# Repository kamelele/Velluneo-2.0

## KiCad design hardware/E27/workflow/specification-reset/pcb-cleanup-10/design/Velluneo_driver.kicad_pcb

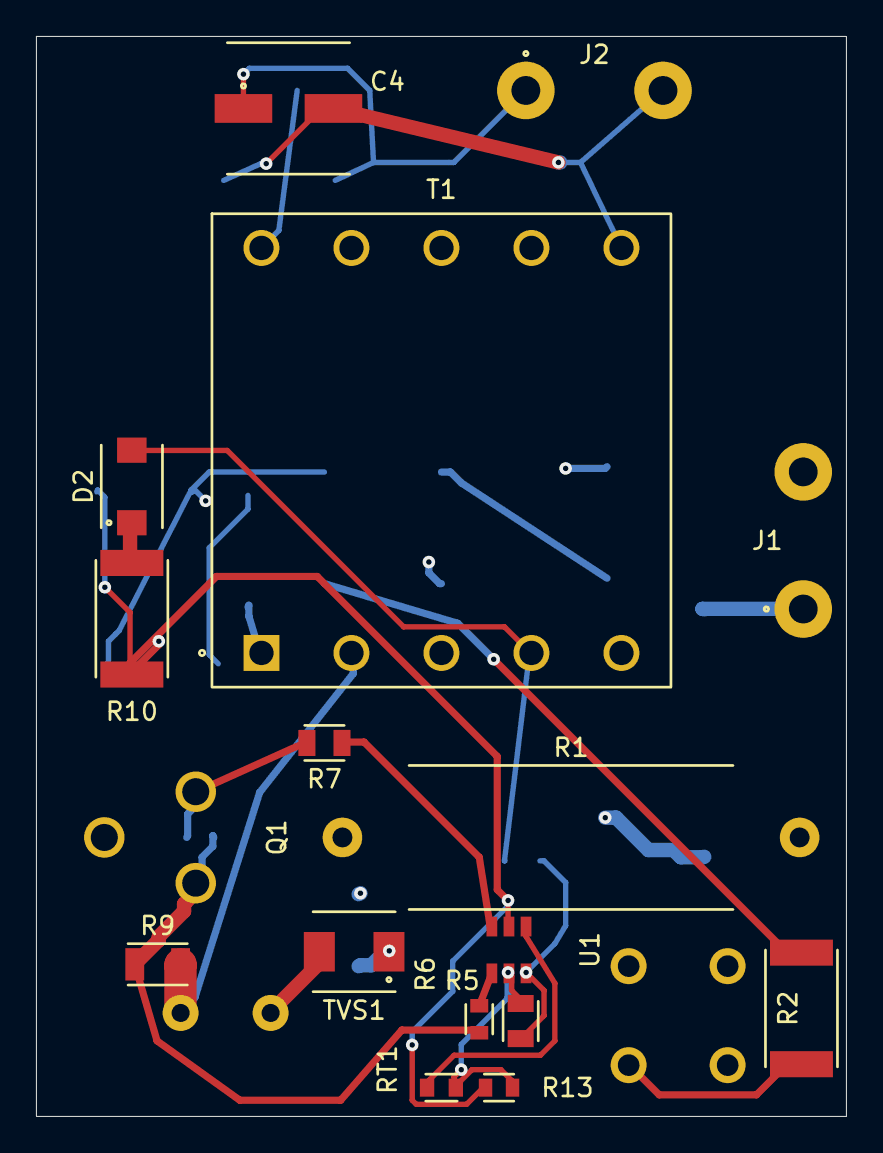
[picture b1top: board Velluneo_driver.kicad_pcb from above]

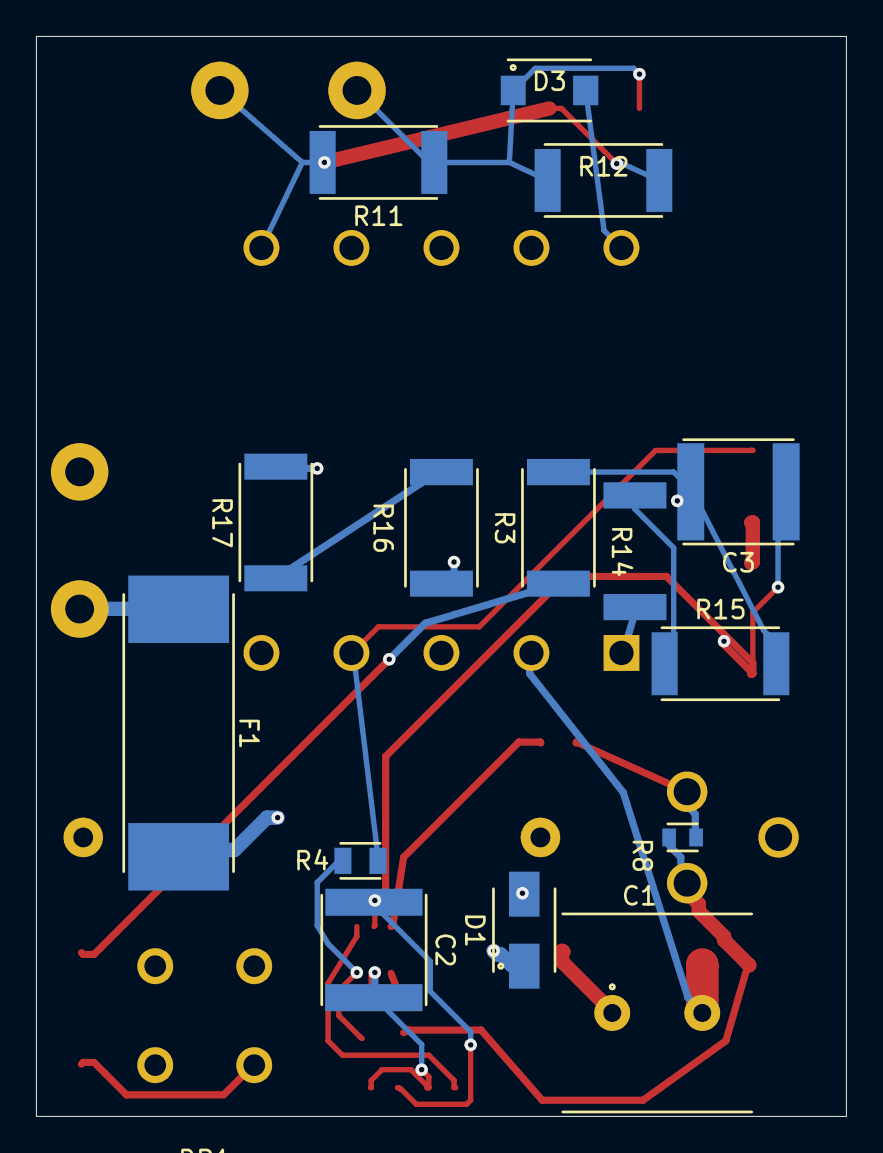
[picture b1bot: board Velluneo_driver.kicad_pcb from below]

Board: 4 copper layers, 45.0 x 60.0 mm, 33 parts (16 on the bottom side), 23 nets.

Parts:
BR1: W10G-E4/51; W10G_Formed5p5_PROJECT
C1: 15u / 450V; Rubycon_BXW_D10_P5_PROJECT_CANDIDATE
C2, C3: 470n / 50V C0G; KEMET_2220_C0G_DensityB_Native
C4: 10u / 63V HYBRID; Panasonic_ZA_D_Standard_Native
D1: US1M-13-F; Diodes_US1M_SMA_Native
D2: STTH1R02A; ST_STTH_SMA_Native
D3: STTH2R02A; ST_STTH_SMA_Native
F1: 250mA / 277VAC; SCHURTER_UMTH_WEB_PROVISIONAL
J1: E27 INTERNAL WIRES; InternalWirePair_P7p62_D1p6_PROJECT_CANDIDATE
J2: INTERNAL LED WIRES; InternalWirePair_P7p62_D1p6_PROJECT_CANDIDATE
Q1: STF2N80K5; STF2N80K5_Stagger5p08_Pad2p25_PROJECT
R1: 47R / AC05; AC05_P25p4_FORMED_PROJECT_CANDIDATE
R2, R3, R15: 499k; CRCW_2512_NativeReflow
R4: 80.6k; CRCW_0805_NativeReflow
R5: 17.4k; CRCW_0805_NativeReflow
R6: 1.40k; CRCW_0603_NativeReflow
R7: 4.7R; CRCW_0805_NativeReflow
R8: 47k; CRCW_0603_NativeReflow
R9: 2.32R / PROPOSED; CRCW_1206_NativeReflow
R10: 4.7R; CRCW_2512_NativeReflow
R11, R12: 20k; CRCW_2512_NativeReflow
R13: 80.6k / feed bleeder; CRCW_0603_NativeReflow
R14: 499k; CRCW_2512_R14_SilkClear
R16, R17: 402k / startup; CRCW_2512_NativeReflow
RT1: 100k / B4100; NTCS0603_NativeReflow
T1: 120:30:22 / 2.304mH; TDK_EFD25_Pad2p0_PROJECT
TVS1: SMBJ160A-E3/52; Vishay_SMBJ_PROJECT_CANDIDATE
U1: UCC28701DBVR; UCC28701_DBV_Native

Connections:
/AUX_RAW: D2.2, R4.1, T1.4
/BLEED_MID_B: R14.2, R15.1
/BULK_POS: BR1.1, C1.1, R2.1, R14.1, R16.1, T1.1, TVS1.2
/CS: R6.2, U1.4
/DRAIN: D1.2, Q1.2, T1.5
/DRV: R7.1, U1.3
/GATE: Q1.1, R7.2, R8.1
/NTC: RT1.1, U1.1
/OUTPUT_NEG: C4.2, J2.2, R11.2, R12.2, T1.6
/OUTPUT_POS: C4.1, D3.1, J2.1, R11.1, R12.1
/PRIMARY_GND: BR1.3, C1.2, C2.2, C3.2, R3.2, R5.2, R9.2, R13.2, R15.2, RT1.2, T1.2, U1.5
/SECONDARY_RAW: D3.2, T1.10
/SENSE: Q1.3, R6.1, R8.2, R9.1
/STARTUP_MID: R16.2, R17.1
/VDD: C2.1, C3.1, R10.2, R13.1, R17.2, U1.2
/VS: R4.2, R5.1, U1.6
unnamed: BR1.2, J1.2
unnamed: BR1.4, R1.2
unnamed: D1.1, TVS1.1
unnamed: D2.1, R10.1
unnamed: F1.1, J1.1
unnamed: F1.2, R1.1
unnamed: R2.2, R3.1

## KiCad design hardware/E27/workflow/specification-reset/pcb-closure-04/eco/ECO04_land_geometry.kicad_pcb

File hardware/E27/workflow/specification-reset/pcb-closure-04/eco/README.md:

# ECO04 — concrete, unapplied spacing redesign

This is a **proposed33-part/81-pin electrical and terminal-construction change**, not the approved31-part driver and a complete proposed placed PCB, with no tracks. The separate native schematic, BOM, pre-CAD pin map, fresh81-pin/23-functional-net comparison and four footprint coupons are supplied for affected review. Human approval is absent. The improved31-part return-layout project in the parent directory still reports the eight package clearance findings.

## Exact proposed changes

- U1: UCC28711DR → **UCC28701DBVR**, a real no-HV-pin controller. New pin numbers are1NTC,2VDD,3DRV,4CS,5GND,6VS. Add R16/R17, each proposed402kΩ/2512, in series BULK_POS → STARTUP_MID → VDD. This physically removes the old high-voltage pin pair; it is not an artificial net rename or NC flag.
- R13: **80.6kΩ CRCW060380K6FKEA**, replacing1MΩ, forms a passive divider with804kΩ startup resistance. At normal253Vac and±2.1% resistor allowances, its zero-controller-current ceiling is33.8667V. This addresses the continuous startup-feed bound without assuming a minimum IC sink current. It is not a clamp on auxiliary/transient/surge injection.
- R9: proposed **2.32Ω E96 CRCW12062R32FKEA**, subject to procurement confirmation, replacing2.37Ω to account for the new CC constant. Nominal current changes about−1.25%, rather than falsely claiming pin-for-pin electrical equivalence. The earlier2.29Ω mathematical target was not silently treated as an available catalog part.
- BR1: **W10G-E4/51**, with a proposed formed5.5±0.05mm grid,2.0mm pads/1.2mm holes. Raw leads are not fixed5.08mm; forming/registration, polarity datum and supplier process require qualification. Nominal adjacent copper gap3.5mm, annulus0.4mm.
- Q1: **STF2N80K5**, G1/D2/S3, replacing the SOT223 device and separate drain-tab terminal. Proposed outer-terminal rowy0/centre drainy5.08mm at2.54mmx pitch,2.2mm pads/1.5mm holes. Nominal G-D and D-S gap3.479613mm; annulus0.35mm. Bend radius, root clearance, seating, strain, jig and installed height are unresolved process inputs.
- T1: proposed project lands2.0mm rather than2.4mm, with the same1.35mm finished holes and5mm pitch. Nominal annulus0.325mm and copper gap3.0mm. This is an explicit land redesign, not a source-prescribed qualified transformer or a claim that solder/registration tolerances leave3mm finished insulation.

The four isolated native land coupons have **zero native DRC violations**, with four unconnected items/exit5. They are not a functional supply. No3mm limit was reduced; primary/secondary remains10mm and STARTUP_MID is explicitly included as primary/HV in the proposed coupon rule scope. This result establishes nominal land geometry only. It does not clear the eight findings on the unchanged31-part driver or by itself prove a complete33-part placement; see the separately checked full-board r3 result below.

## Source and operating differences

[TI UCC2870x](https://www.ti.com/lit/ds/symlink/ucc28700.pdf), SLUSB41A, pp3–6/12/21/24: no-HV NTC variant, UVLO19–23V/on and7.7–8.45V/off, startup1.5µA maximum at18V, CC constant310/319/329mV, new120/130/140kHz ceiling. NTC0.95V/105µA are typical only; the old bounded NTC resistance window and106kHz magnetic/thermal assessment cannot transfer. Recommended temperature starts−20C. [TI DBV land example](https://www.ti.com/lit/pdf/mpds026), p2: six1.1×0.6mm pads,x±1.3/y±0.95/0. These facts require a real controller ECO, not a drop-in claim.

[Vishay W10G](https://www.vishay.com/docs/88769/w005g.pdf), document88769, pp1–3:1000V/1.5A family, rawleadØ0.71–0.81mm/pitch4.6–5.6mm. Its current/thermal test conditions are not transferred to the new forming/land process. [ST STF2N80K5](https://www.st.com/resource/en/datasheet/stf2n80k5.pdf), DS14533rev1, pp1–3/9–10:800V,4.5Ωmax at10V/1A, Qg5nCtyp/Ciss105pFtyp, rectangular lead max1.00×0.70mm. Proposed hole accommodates that section; it does not qualify formed leads or switching/thermal performance.

Native source download of ST timed out twice; source facts above were inspected through official PDF text and independently checked by the source implementer, not a fabricated locally hashed PDF. Coupon coordinates beyond manufacturer land examples are explicitly project constructions. Exact existing-source hashes and native artifacts are frozen with the packet.

## Corrected startup and current calculations

calculate.py includes **both C2/C3 directly across VDD**, total0.94µF, old R13=1MΩ for rejected proposals and proposed80.6kΩ for the revised circuit, plus reverse D2 leakage. The auxiliary series resistor is R10=4.7Ω. The first13.6MΩ suggestion is explicitly rejected: its equilibrium18.65V at207Vac cannot reach23V even without diode leakage. Revised804kΩ/80.6kΩ is screened over resistor±2.1%, capacitor±5%, diode3/20µA and0/5V bulk-drop assumptions. These are loaded DC charging calculations, not demonstrated mains startup or a complete guaranteed controller model. [STTH1R02 leakage data](https://www.st.com/resource/en/datasheet/stth1r02.pdf), DS4743rev4p2, is conditional on rated reverse voltage and25/125C.

The nominal current equation is RCS=VCCR×NPS×η/(2×Iout), including the factor2. New2.32Ω gives approximately0.2475A atNPS4/η0.9. Normal energy/DCM screens and gate-energy scale are calculated explicitly; they are not a guaranteed fault ceiling, core-loss, SOA, repetitive clamp or temperature result. No minimum controller fault draw is specified, so no guaranteed retry interval is invented.

## Acceptance boundary

Power/magnetic/thermal review must close new frequency/control/corners, actual VDD behavior, NTC/sensor faults and repetitive/fault stresses. Mechanical/process review must validate lead forming, polarity, tolerances, finished solder/hole/annulus/insulation and installed envelope. The coupon does not establish fit inside40x60 or an outerØ60x120 lamp. The complete proposed replacement PCB has now been drafted in isolation; independent review and the human intent decision are required before adoption and accepted routing. Passing ERC or coupon DRC supplies neither that decision nor electrical/safety qualification.

## R2 review correction — VDD feed ceiling and inventory

Independent Reality finding R-C04-01 identified a real omission after the first charging calculation: the4.42MΩ/1MΩ continuous feed has a66.01V zero-controller-current equilibrium at ideal high line. Passing a23V startup screen did not bound VDD. That resistor pair is rejected for adoption. R2 uses two402kΩ startup resistors and80.6kΩ bleed. The passive feed-only normal-line ceiling is33.8667V with±2.1% resistor allowances; the feed net current at35V is negative even with zero controller current. All64 declared loaded charging cases reach23V, worst0.251660s. These are actual executable DC screens, not mains/winding/fault/transient measurements.

High-line resistor dissipation increases from0.02896W to0.15923W atVDD0, an additional0.13027W that remains an explicit thermal/lifetime condition. No active regulator, invented minimum current or stability claim is used. The gate-drive/auxiliary source and transient ceiling, retry, newNTCparameters/140kHzbehavior and finishedconstruction remain open. Change review also caught a reproducibility defect: the coupon builder now preserves both local library-table entries needed by the separate proposed schematic. Native31-part driver CAD is unchanged by this review correction.

## R3 — complete proposed PCB, not just coupons

Velluneo_specification_reset.kicad_pro now opens the complete proposed **33-part/81-pad rectangular41x60mm PCB and matched schematic**. Full native KiCad10.0.6 DRC with schematic parity has **zero violations, zero parity findings and54unconnected items**. It exits5 because it is unrouted, with zero tracks/vias. Coupon results remain separate. No global numeric clearance limit or source severity was weakened:3mm functional screen,10mm P/S reservation including allNC,0.25mm general and0.5mm copper-edge remain. Every loaded/reloaded pad shape/attribute/drill/layer/position, MPN/value/FPID/net and canonical pre-CAD intent agrees; source-module hashes bind the planning inventory. The original eight reports remain only on the retained old31-part comparison board, not on this new candidate.

The full proposal passes0.1mm same-face courtyard,0.4mm opposite THT-joint allowance, full30x30mm T1 allocation/semiconductor exclusion and all81-pad shape-aware common-copper checks. Independent native positive/negative circle controls confirm nominal Q1gap3.479613mm versus deliberate2.708319mm failure under the unchanged3mm rule. The deliberate negative fixture also reports the expected library mismatch; no production module was changed by the diagnostic. R3/R14 moved+0.10/-0.05mm inX to remove native outline-artwork collision without changing libraries or copper.

TVS-to-C1 return is **4.472027mm**, versus25.900622mm in the prior40mm alternate and12.470815mm in the retained31-part correction. Q1–D1–TVS–C1 chain20.996621mm, T1 clamp three-leg sum38.812533mm. Bypass1.35mm both sides, CS2.059mm, gate3.384mm, power-shunt5.642mm and shunt-ground return2.7mm. **R6-to-R9 sense endpoint is19.906mm: a disclosed regression.** Dedicated Kelvin sensing/reference routing and coupling/shared-impedance review are mandatory; do not interpret shorter clamp endpoints as a proof that the full operating layout improved. Three cross-face HV/quiet projections remain unqualified; their exact pairs are in checks/full-scalar.json.

41mm is an engineering trial,1mm wider than the last40mm and not an owner-approved finished envelope. A specific Q1/R1 side-by-side arrangement needs about40.5mm; no global proof that every40mm arrangement is impossible is claimed. Actual rotated Fab/declared height allocations yield58.028755mm nominal radial diameter, limitingC1, leaving only0.985623mm radial difference to the60mm OUTER target. Walls, mounting, wire, tolerances, seating/forming and120mm assembly fit are not established. All33models are unqualified allocations, not vendor construction proofs.

This is a concrete reviewable ECO proposal. New controller/startup/NTC/frequency/thermal/magnetic/fault behavior, terminal forming, finished insulation and genuine affected-stage decisions remain open. Zero nominal placement DRC does not establish accepted routing, electrical safety or manufacturing readiness. See routing-intent.md for next-stage constraints. No Gerbers, ordering, supplier contact or powered test is authorized or performed.

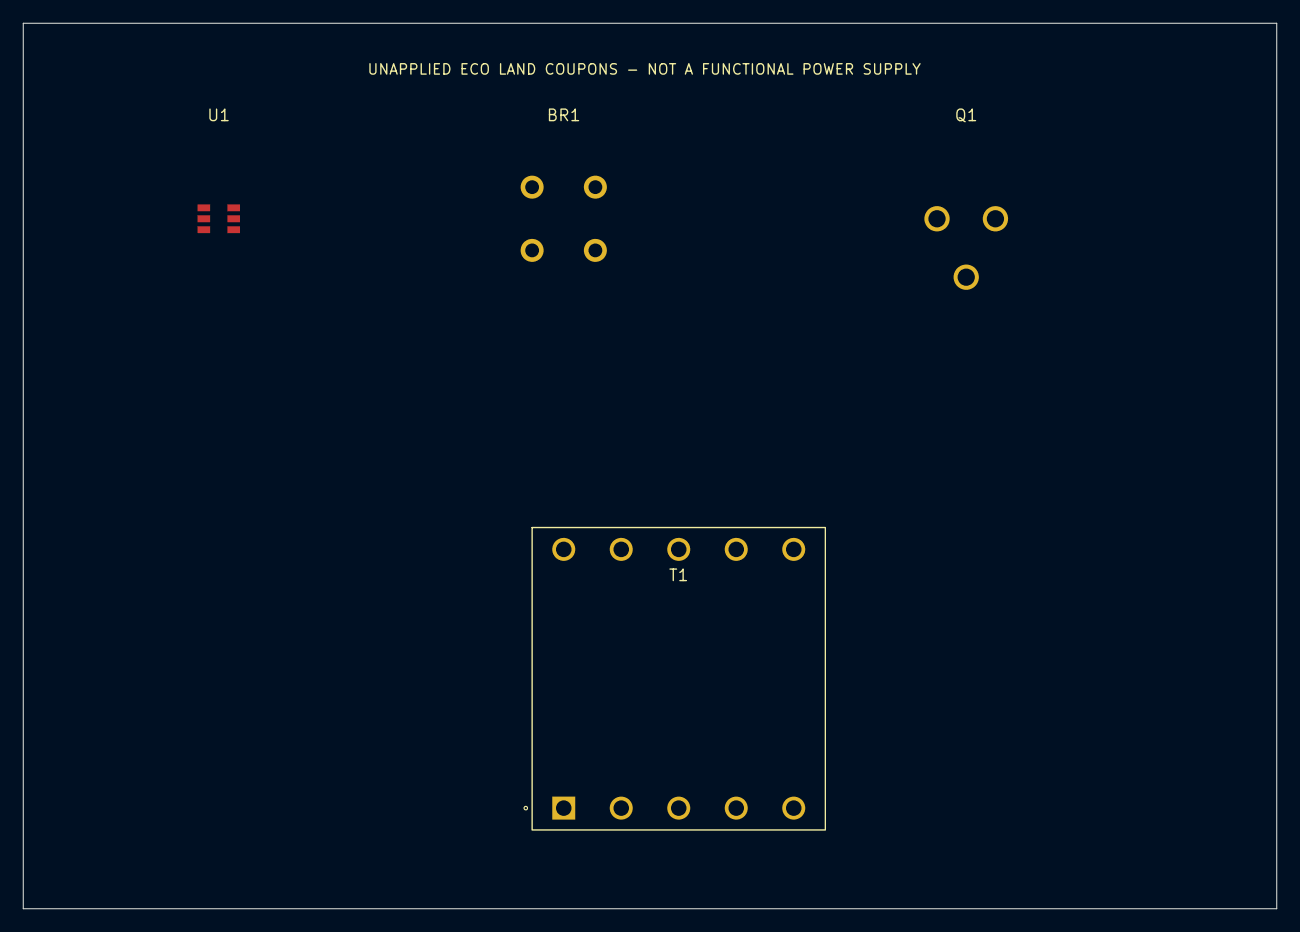
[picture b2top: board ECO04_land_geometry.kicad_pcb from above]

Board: 2 copper layers, 109.0 x 77.0 mm, 4 parts (0 on the bottom side), 3 nets, no tracks yet.

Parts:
BR1: W10G-E4/51; W10G_Formed5p5_PROJECT
Q1: STF2N80K5; STF2N80K5_Stagger5p08_PROJECT
T1: CUSTOM:EFD25_120_30_22; TDK_EFD25_Pad2p0_PROJECT
U1: UCC28701DBVR; UCC28701_DBV_Native

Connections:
/BULK_POS: BR1.1, T1.1
/DRAIN: Q1.2, T1.5
/PRIMARY_GND: BR1.3, T1.2, U1.5

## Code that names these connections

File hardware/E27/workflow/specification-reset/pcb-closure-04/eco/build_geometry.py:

"""Unapplied component/terminal ECO coupons, NOT a functional replacement supply."""
from pathlib import Path
import json,math,hashlib,copy
import pcbnew
D=Path(__file__).resolve().parent;P=D.parents[1];ROOT=D.parent;L=D/'Velluneo_ECO04.pretty';L.mkdir(exist_ok=True)
def module(name,pads,court,fab,descr):
 s=f'(footprint "{name}" (version 20241229) (generator "velluneo_eco04") (layer "F.Cu") (descr "{descr}") '
 s+='(attr '+('through_hole'if any(p[-1]for p in pads)else'smd')+')'
 s+='(property "Reference" "REF**" (at 0 -8) (layer "F.SilkS") (effects (font (size 1 1) (thickness .12))))'
 s+=f'(property "Value" "{name}" (at 0 9) (layer "F.Fab") (effects (font (size 1 1))))'
 for bb,layer in((court,'F.CrtYd'),(fab,'F.Fab')):s+=f'(fp_rect (start {bb[0]} {bb[1]}) (end {bb[2]} {bb[3]}) (stroke (width .05) (type default)) (fill none) (layer "{layer}"))'
 for n,x,y,w,h,drill in pads:
  if drill:s+=f'(pad "{n}" thru_hole circle (at {x} {y}) (size {w} {h}) (drill {drill}) (layers "*.Cu" "*.Mask"))'
  else:s+=f'(pad "{n}" smd rect (at {x} {y}) (size {w} {h}) (layers "F.Cu" "F.Paste" "F.Mask"))'
 s+=')\n';(L/(name+'.kicad_mod')).write_text(s,encoding='utf-8',newline='\n')
module('UCC28701_DBV_Native',[(1,-1.3,-.95,1.1,.6,0),(2,-1.3,0,1.1,.6,0),(3,-1.3,.95,1.1,.6,0),(6,1.3,-.95,1.1,.6,0),(5,1.3,0,1.1,.6,0),(4,1.3,.95,1.1,.6,0)],[-2.1,-1.55,2.1,1.55],[-.8,-1.45,.8,1.45],'TI DBV0006A native land example; UCC28701 new controller requires full circuit revalidation')
module('W10G_Formed5p5_PROJECT',[(1,-2.75,-2.75,2,2,1.2),(2,2.75,-2.75,2,2,1.2),(3,2.75,2.75,2,2,1.2),(4,-2.75,2.75,2,2,1.2)],[-5.43,-5.43,5.43,5.43],[-4.93,-4.93,4.93,4.93],'PROJECT formed5.5mm grid, not native fixed pitch; polarity datum plus lead NW, AC NE and SW, minus SE; process unqualified')
module('STF2N80K5_Stagger5p08_PROJECT',[(1,-2.54,0,2.2,2.2,1.5),(2,0,5.08,2.2,2.2,1.5),(3,2.54,0,2.2,2.2,1.5)],[-5.7,-5.1,5.7,6.68],[-5.2,-4.6,5.2,0],'PROJECT formed lead stagger G1 D2 S3; root clearance, bend radius, seating and jig unqualified')
src=P/'libraries/Velluneo_Driver.pretty/TDK_B66422W1010D001_EFD25_RAW_CANDIDATE.kicad_mod';s=src.read_text(encoding='utf-8');assert s.count('(size 2.4 2.4)')==10
s=s.replace('TDK_B66422W1010D001_EFD25_RAW_CANDIDATE','TDK_EFD25_Pad2p0_PROJECT').replace('(size 2.4 2.4)','(size 2.0 2.0)');(L/'TDK_EFD25_Pad2p0_PROJECT.kicad_mod').write_text(s,encoding='utf-8',newline='\n')
parts=json.loads((P/'electrical-integration/proposed-parts.json').read_text(encoding='utf-8'));by={p['ref']:p for p in parts}
by['U1'].update(mpn='UCC28701DBVR',value='PROPOSED no-HV NTC PSR controller',pins={'1':'NTC','2':'VDD','3':'DRV','4':'CS','5':'PRIMARY_GND','6':'VS'})
by['Q1'].update(mpn='STF2N80K5',value='PROPOSED 800V TO220FP formed terminals',pins={'1':'GATE','2':'DRAIN','3':'SENSE'})
by['BR1'].update(mpn='W10G-E4/51',value='PROPOSED 1000V bridge, formed grid')
by['R9'].update(mpn='CRCW12062R32FKEA',value='PROPOSED 2.32ohm, E96; procurement unconfirmed')
by['R13'].update(mpn='CRCW060380K6FKEA',value='PROPOSED 80.6kohm VDD feed bleeder')
parts.extend([dict(ref='R16',mpn='CRCW2512402KFKEG',value='PROPOSED 402kohm startup',pins={'1':'BULK_POS','2':'STARTUP_MID'}),dict(ref='R17',mpn='CRCW2512402KFKEG',value='PROPOSED 402kohm startup',pins={'1':'STARTUP_MID','2':'VDD'})])
assert len(parts)==33 and sum(len(p['pins'])for p in parts)==81
(D/'proposed-parts.json').write_text(json.dumps(parts,indent=2)+'\n',encoding='utf-8',newline='\n')
mapping={'U1':'UCC28701_DBV_Native','BR1':'W10G_Formed5p5_PROJECT','Q1':'STF2N80K5_Stagger5p08_PROJECT','T1':'TDK_EFD25_Pad2p0_PROJECT'}
board=pcbnew.BOARD();board.SetCopperLayerCount(2);board.GetDesignSettings().SetBoardThickness(pcbnew.FromMM(1.6))
aliases=json.loads((ROOT/'checks/board-parity.json').read_text(encoding='utf-8'))['logical_to_native_netnames'];nets={}
for p in parts:
 for n in p['pins'].values():
  if n is not None and n not in nets:
   net=pcbnew.NETINFO_ITEM(board,aliases.get(n,'/'+n));board.Add(net);nets[n]=net
def pt(x,y):return pcbnew.VECTOR2I(pcbnew.FromMM(x),pcbnew.FromMM(y))
for ref,(x,y)in {'U1':(20,20),'BR1':(50,20),'Q1':(85,20),'T1':(60,60)}.items():
 fp=pcbnew.FootprintLoad(str(L),mapping[ref]);assert fp;fp.SetReference(ref);fp.SetValue(by[ref]['mpn']);fp.SetFPID(pcbnew.LIB_ID('Velluneo_ECO04',mapping[ref]));fp.SetPosition(pt(x,y));board.Add(fp)
 for pad in fp.Pads():
  n=by[ref]['pins'][pad.GetNumber()]
  if n is None:
   net=pcbnew.NETINFO_ITEM(board,f'unconnected-(T1-Pad{pad.GetNumber()})');board.Add(net);pad.SetNet(net)
  else:pad.SetNet(nets[n])
 fp.Reference().SetTextSize(pt(1,1));fp.Reference().SetTextThickness(pcbnew.FromMM(.12));fp.Reference().SetPosition(pt(x,y-9));fp.Reference().SetVisible(True)
for a,b in [((3,3),(112,3)),((112,3),(112,80)),((112,80),(3,80)),((3,80),(3,3))]:
 e=pcbnew.PCB_SHAPE();e.SetShape(pcbnew.SHAPE_T_SEGMENT);e.SetLayer(pcbnew.Edge_Cuts);e.SetStart(pt(*a));e.SetEnd(pt(*b));e.SetWidth(pcbnew.FromMM(.05));board.Add(e)
text=pcbnew.PCB_TEXT(board);text.SetText('UNAPPLIED ECO LAND COUPONS - NOT A FUNCTIONAL POWER SUPPLY');text.SetLayer(pcbnew.F_SilkS);text.SetTextSize(pt(.9,.9));text.SetTextThickness(pcbnew.FromMM(.12));text.SetPosition(pt(57,7));board.Add(text)
path=D/'ECO04_land_geometry.kicad_pcb';pcbnew.SaveBoard(str(path),board)
rules=(ROOT/'Velluneo_specification_reset.kicad_dru').read_text(encoding='utf-8')
for k in('A','B'):rules=rules.replace(f"{k}.NetName == '/BULK_POS'",f"({k}.NetName == '/BULK_POS' || {k}.NetName == '/STARTUP_MID')")
(D/'ECO04_land_geometry.kicad_dru').write_text(rules,encoding='utf-8',newline='\n')
(D/'fp-lib-table').write_text('(fp_lib_table (version 7) (lib (name "Velluneo_ECO04") (type "KiCad") (uri "${KIPRJMOD}/Velluneo_ECO04.pretty") (options "") (descr "Unapplied proposed ECO land geometry")) (lib (name "Velluneo_Driver") (type "KiCad") (uri "${KIPRJMOD}/libraries/Velluneo_Driver.pretty") (options "") (descr "Retained passive lands")))\n',encoding='utf-8',newline='\n')
(D/'ECO04_land_geometry.kicad_pro').write_text(json.dumps({'board':{'design_settings':{'rules':{'min_clearance':.25,'min_track_width':.3,'min_via_diameter':.6,'min_through_hole_diameter':.3,'min_copper_edge_clearance':.5}}}},indent=2)+'\n',encoding='utf-8',newline='\n')
rows=[dict(object='BR1 formed adjacent lands',nominal_gap_mm=3.5,annulus_mm=.4,qualified=False),dict(object='Q1 formed G-D and D-S',nominal_gap_mm=math.hypot(2.54,5.08)-2.2,annulus_mm=.35,qualified=False),dict(object='T1 adjacent project lands',nominal_gap_mm=3.,annulus_mm=.325,qualified=False),dict(object='U1 former HV-DRV pair',nominal_gap_mm=None,reason='High-voltage pin physically absent on new controller; real circuit/startup ECO, not a new net label',qualified=False)]
(D/'geometry-contract.json').write_text(json.dumps(dict(status='Unapplied proposal',part_count_proposed=33,pads_proposed=81,coupon_footprints=4,coupon_pads=23,pairs=rows,pin_mapping=mapping,scope='These isolated land coupons are not a complete placed/functional33-part driver. No routing/safety/assembly or source-process approval. Original driver remains31parts/79pads and retains its8clearance failures.'),indent=2)+'\n',encoding='utf-8',newline='\n')
print(json.dumps(dict(proposed_parts=33,proposed_pads=81,coupon_footprints=4,coupon_pads=23,saved=str(path),functional_board=False)))
